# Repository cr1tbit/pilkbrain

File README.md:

# pilkbrain

The schematic is still a bit messy, just for the reference for now.

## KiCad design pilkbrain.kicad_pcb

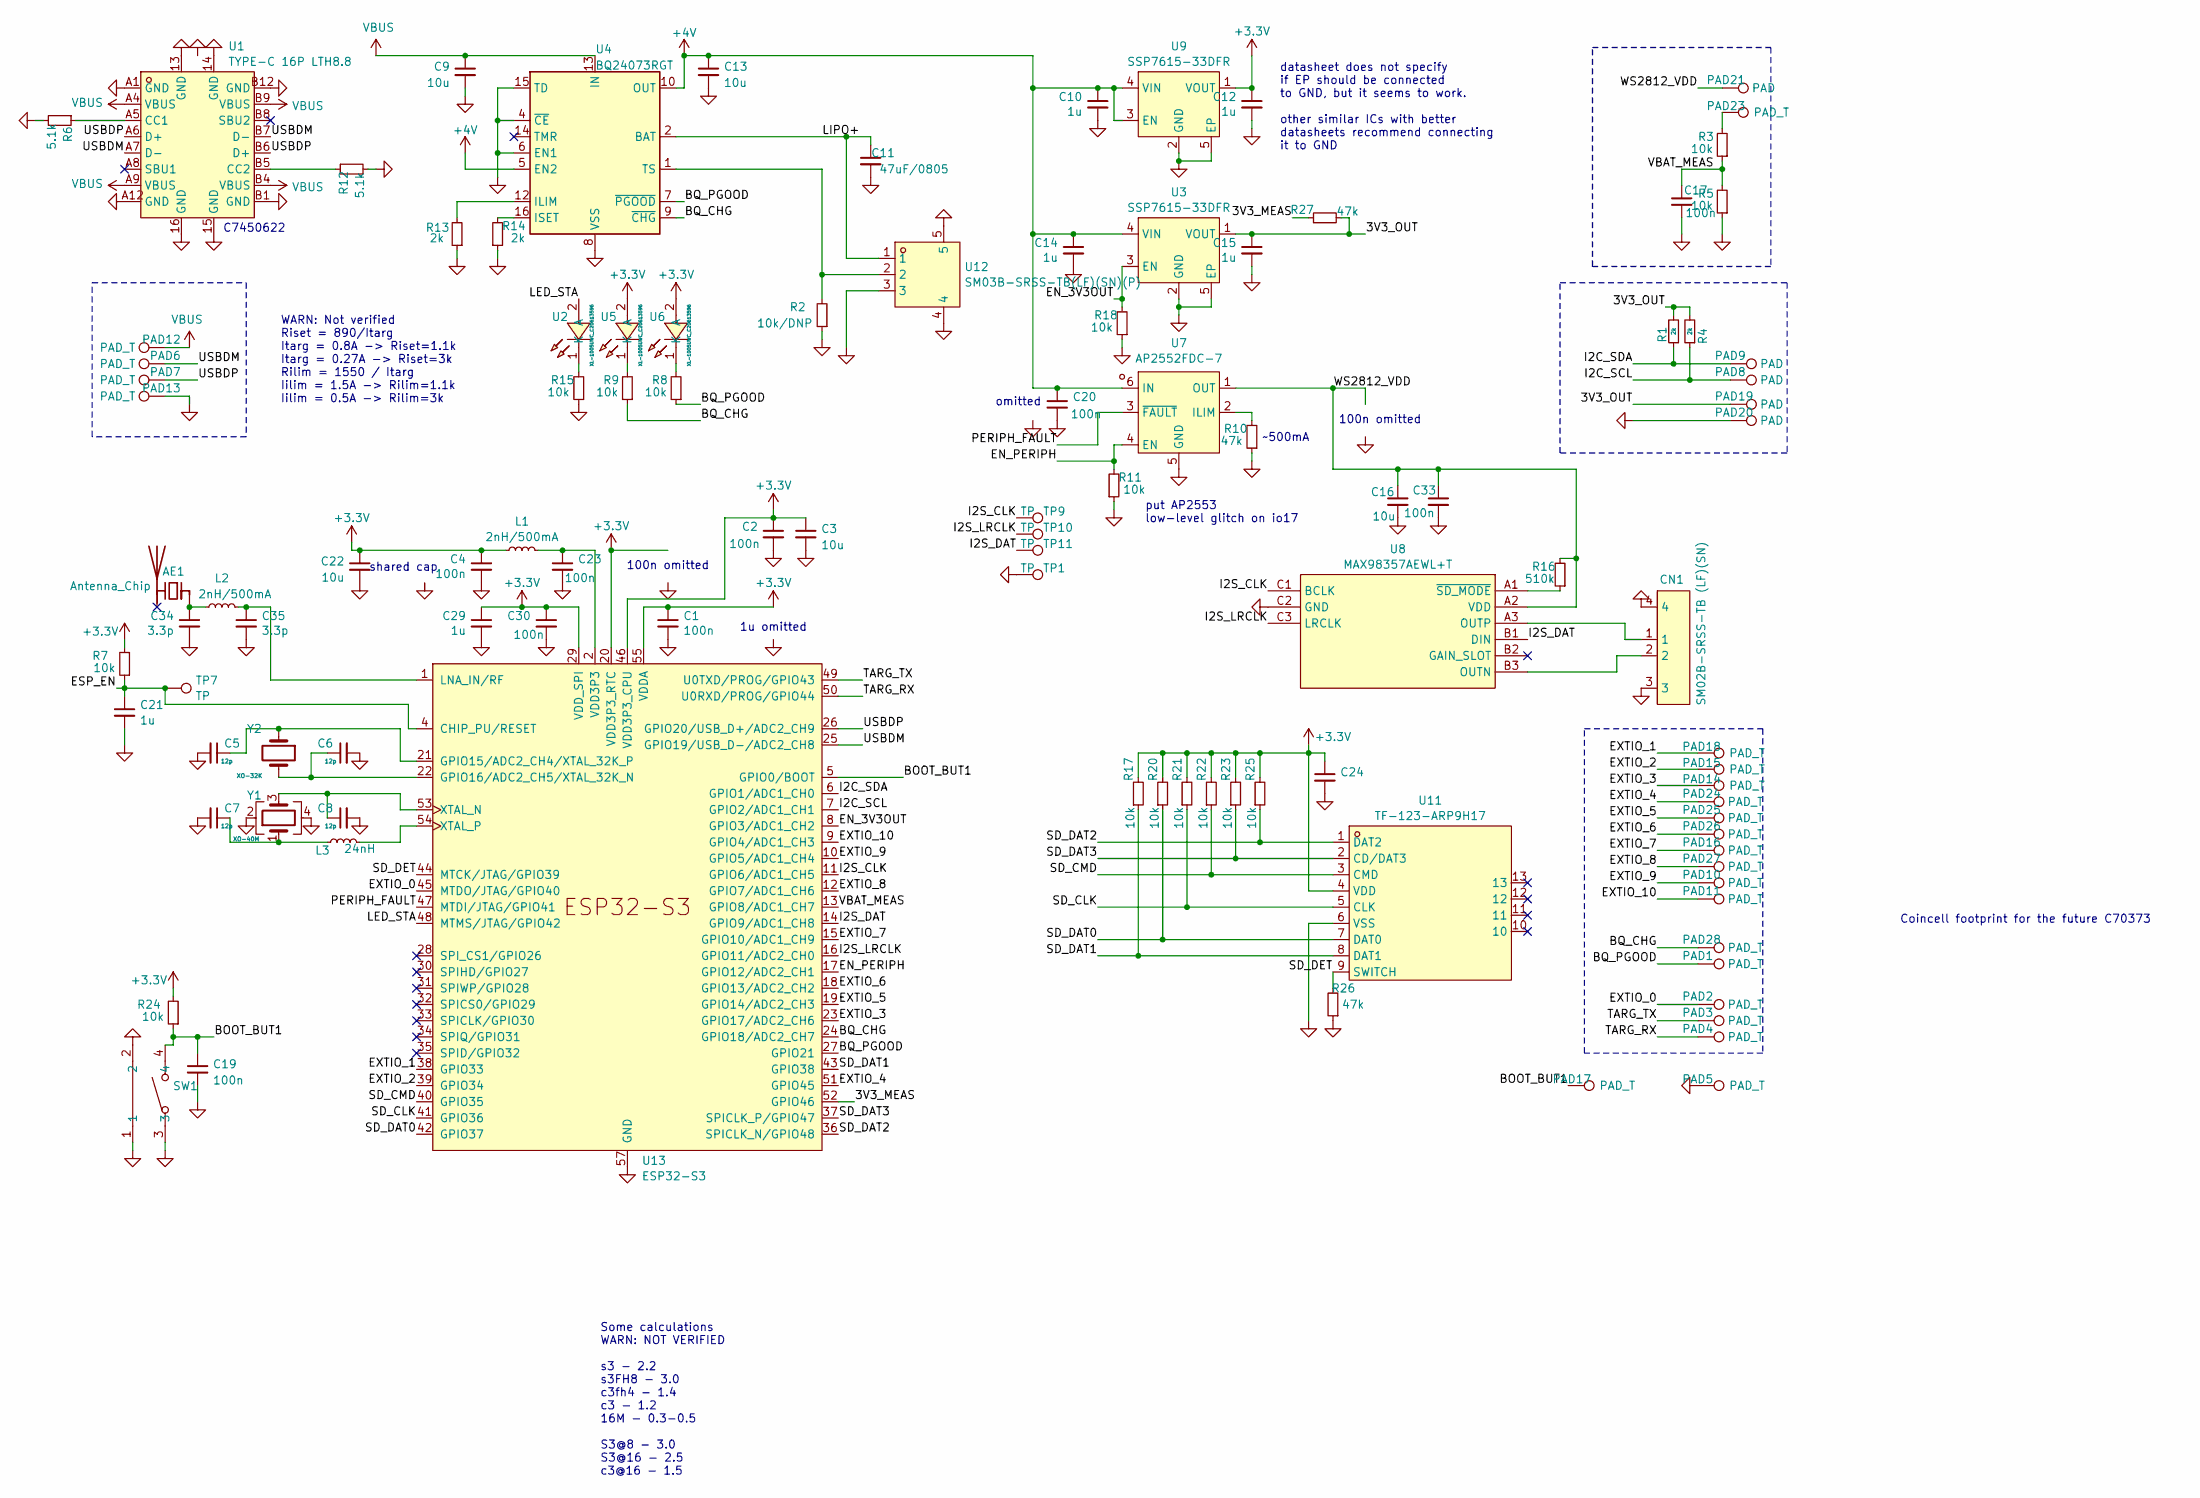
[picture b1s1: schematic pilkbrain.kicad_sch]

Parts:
AE1: Antenna_Chip; Johanson_2450AT18x100; LCSC C127629
C1, C2, C4, C17, C19, C20, C23, C24, C30, C33: 100n; C_0402_1005Metric; LCSC C1525
C3, C9, C13, C16, C22: 10u; C_0402_1005Metric; LCSC C15525
C5, C6, C7, C8: 12p; C_0402_1005Metric; LCSC C1547
C10, C12, C14, C15, C21, C29: 1u; C_0402_1005Metric; LCSC C52923
C11: 47uF/0805; C_0805_2012Metric; LCSC C16780
C34, C35: 3.3p; C_0402_1005Metric; LCSC C1565
CN1: SM02B-SRSS-TB (LF)(SN); CONN-SMD_2P-P1.00_SM02B-SRSS-TB-LF-SN; LCSC C160402
L1, L2: 2nH/500mA; L_0402_1005Metric; LCSC C97984
L3: 24nH; L_0402_1005Metric; LCSC C330863
PAD1, PAD2, PAD3, PAD4, PAD5, PAD6, PAD7, PAD10, PAD11, PAD12, PAD13, PAD14, PAD15, PAD16, PAD17, PAD18, PAD23, PAD24, PAD25, PAD26, PAD27, PAD28: PAD_T; diy_castellate_tight
PAD8, PAD9, PAD19, PAD20, PAD21: PAD; diy_castellate_2.54
R1, R4, R13, R14: 2k; R_0402_1005Metric
R2: 10k/DNP; R_0603_1608Metric
R3, R5, R7, R8, R9, R11, R15, R17, R18, R20, R21, R22, R23, R24, R25: 10k; R_0402_1005Metric
R6, R12: 5.1k; R_0402_1005Metric
R10, R26, R27: 47k; R_0402_1005Metric
R16: 510k; R_0603_1608Metric
SW1: TS24CA; SW-SMD_TS24CA; LCSC C393942
TP1, TP7, TP9, TP10, TP11: TP; TestPoint_Pad_D1.0mm
U1: TYPE-C 16P LTH8.8; USB-C-SMD_TYPE-C-16P-LTH8.8; LCSC C5187469
U2, U5, U6: XL-1005UWC_C20613596; LED0402-RD_YELLOW; LCSC C20613596
U3, U9: SSP7615-33DFR; DFN-4_L1.0-W1.0-P0.65-BL-EP; LCSC C3011523
U4: BQ24073RGT; VQFN-16-1EP_3x3mm_P0.5mm_EP1.6x1.6mm_ThermalVias; LCSC C15220
U7: AP2552FDC-7; WDFN-6_L2.0-W2.0-P0.65-BL-EP-1; LCSC C211419
U8: MAX98357AEWL+T; WLP-9_L1.4-W1.3-P0.40-R3-C3-BR; LCSC C2682619
U11: TF-123-ARP9H17; TF-SMD_TF-123-ARP9H15; LCSC C2982548
U12: SM03B-SRSS-TB(LF)(SN)(P); CONN-SMD_SM03B-SRSS-TB-LF-SN-P; LCSC C160403
U13: ESP32-S3; QFN-56-1EP_7x7mm_P0.4mm_EP5.6x5.6mm; LCSC C3013940
Y1: XO-40M; Crystal_SMD_2520-4Pin_2.5x2.0mm; LCSC C2885592
Y2: XO-32K; Crystal_SMD_2012-2Pin_2.0x1.2mm; LCSC C7500573

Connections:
+3.3V: C1.1, C2.1, C3.1, C4.1, C12.1, C22.1, C24.1, C29.1, C30.1, L1.1, R7.2, R17.2, R20.2, R21.2, R22.2, R23.2, R24.2, R25.2, U5.2 (A), U6.2 (A), U9.1 (VOUT), U11.4 (VDD), U13.20 (VDD3P3_RTC), U13.29 (VDD_SPI), U13.46 (VDD3P3_CPU), U13.55 (VDDA), U13.56 (VDDA)
+4V: C10.1, C13.1, C14.1, C20.1, U3.4 (VIN), U4.5 (EN2), U4.10 (OUT), U4.11 (OUT), U7.6 (IN), U9.3 (EN), U9.4 (VIN)
/3V3_MEAS: R27.1, U13.52 (GPIO46)
/3V3_OUT: C15.1, PAD19.1, R1.2, R4.2, R27.2, U3.1 (VOUT)
/BOOT_BUT1: C19.1, PAD17.1, R24.1, SW1.4, U13.5 (GPIO0/BOOT)
/BQ_CHG: PAD28.1, R9.1, U4.9 (~CHG), U13.24 (GPIO18/ADC2_CH7)
/BQ_PGOOD: PAD1.1, R8.1, U4.7 (~PGOOD), U13.27 (GPIO21)
/EN_3V3OUT: R18.2, U3.3 (EN), U13.8 (GPIO3/ADC1_CH2)
/EN_PERIPH: R11.2, U7.4 (EN), U13.17 (GPIO12/ADC2_CH1)
/ESP_EN: C21.1, R7.1, TP7.1, U13.4 (CHIP_PU/RESET)
/EXTIO_0: PAD2.1, U13.45 (MTDO/JTAG/GPIO40)
/EXTIO_1: PAD18.1, U13.38 (GPIO33)
/EXTIO_2: PAD15.1, U13.39 (GPIO34)
/EXTIO_3: PAD14.1, U13.23 (GPIO17/ADC2_CH6)
/EXTIO_4: PAD24.1, U13.51 (GPIO45)
/EXTIO_5: PAD25.1, U13.19 (GPIO14/ADC2_CH3)
/EXTIO_6: PAD26.1, U13.18 (GPIO13/ADC2_CH2)
/EXTIO_7: PAD16.1, U13.15 (GPIO10/ADC1_CH9)
/EXTIO_8: PAD27.1, U13.12 (GPIO7/ADC1_CH6)
/EXTIO_9: PAD10.1, U13.10 (GPIO5/ADC1_CH4)
/EXTIO_10: PAD11.1, U13.9 (GPIO4/ADC1_CH3)
/I2C_SCL: PAD8.1, R4.1, U13.7 (GPIO2/ADC1_CH1)
/I2C_SDA: PAD9.1, R1.1, U13.6 (GPIO1/ADC1_CH0)
/I2S_CLK: TP9.1, U8.C1 (BCLK), U13.11 (GPIO6/ADC1_CH5)
/I2S_DAT: TP11.1, U8.B1 (DIN), U13.14 (GPIO9/ADC1_CH8)
/I2S_LRCLK: TP10.1, U8.C3 (LRCLK), U13.16 (GPIO11/ADC2_CH0)
/LED_STA: U2.2 (A), U13.48 (MTMS/JTAG/GPIO42)
/LIPO+: C11.1, U4.2 (BAT), U4.3 (BAT), U12.1
/PERIPH_FAULT: U7.3 (~FAULT), U13.47 (MTDI/JTAG/GPIO41)
/SD_CLK: R21.1, U11.5 (CLK), U13.41 (GPIO36)
/SD_CMD: R22.1, U11.3 (CMD), U13.40 (GPIO35)
/SD_DAT0: R20.1, U11.7 (DAT0), U13.42 (GPIO37)
/SD_DAT1: R17.1, U11.8 (DAT1), U13.43 (GPIO38)
/SD_DAT2: R25.1, U11.1 (DAT2), U13.36 (SPICLK_N/GPIO48)
/SD_DAT3: R23.1, U11.2 (CD/DAT3), U13.37 (SPICLK_P/GPIO47)
/SD_DET: R26.2, U11.9 (SWITCH), U13.44 (MTCK/JTAG/GPIO39)
/TARG_RX: PAD4.1, U13.50 (U0RXD/PROG/GPIO44)
/TARG_TX: PAD3.1, U13.49 (U0TXD/PROG/GPIO43)
/USBDM: PAD6.1, U1.A7 (D-), U1.B7 (D-), U13.25 (GPIO19/USB_D-/ADC2_CH8)
/USBDP: PAD7.1, U1.A6 (D+), U1.B6 (D+), U13.26 (GPIO20/USB_D+/ADC2_CH9)
/VBAT_MEAS: C17.1, R3.1, R5.2, U13.13 (GPIO8/ADC1_CH7)
/WS2812_VDD: C16.1, C33.1, PAD21.1, R16.2, U7.1 (OUT), U8.A2 (VDD)
GND: C1.2, C2.2, C3.2, C4.2, C5.2, C6.2, C7.2, C8.2, C9.2, C10.2, C11.2, C12.2, C13.2, C14.2, C15.2, C16.2, C17.2, C19.2, C20.2, C21.2, C22.2, C23.2, C24.2, C29.2, C30.2, C33.2, C34.2, C35.2, CN1.3, CN1.4, PAD5.1, PAD13.1, PAD20.1, R2.1, R5.1, R6.2, R10.1, R11.1, R12.2, R13.1, R14.1, R15.1, R18.1, R26.1, SW1.1, SW1.2, SW1.3, TP1.1, U1.13 (GND), U1.14 (GND), U1.15 (GND), U1.16 (GND), U1.A1 (GND), U1.A12 (GND), U1.B1 (GND), U1.B12 (GND), U3.2 (GND), U3.5 (EP), U4.4 (~CE), U4.6 (EN1), U4.8 (VSS), U4.15 (TD), U4.17 (VSS), U7.5 (GND), U7.7 (EXP), U8.C2 (GND), U9.2 (GND), U9.5 (EP), U11.6 (VSS), U12.3, U12.4, U12.5, U13.57 (GND), Y1.2, Y1.4
unnamed: AE1.1 (FEED), C34.1, L2.1
unnamed: C7.1, L3.1, Y1.1
unnamed: PAD23.1, R3.2
unnamed: R6.1, U1.A5 (CC1)
unnamed: R12.1, U1.B5 (CC2)
unnamed: R15.2, U2.1 (K)
unnamed: R13.2, U4.12 (ILIM)
unnamed: R14.2, U4.16 (ISET)
unnamed: R2.2, U4.1 (TS), U12.2
unnamed: R9.2, U5.1 (K)
unnamed: R8.2, U6.1 (K)
unnamed: R10.2, U7.2 (ILIM)
unnamed: CN1.2, U8.B3 (OUTN)
unnamed: CN1.1, U8.A3 (OUTP)
unnamed: R16.1, U8.A1 (~SD_MODE)
unnamed: C5.1, U13.21 (GPIO15/ADC2_CH4/XTAL_32K_P), Y2.1
unnamed: C6.1, U13.22 (GPIO16/ADC2_CH5/XTAL_32K_N), Y2.2
unnamed: C35.1, L2.2, U13.1 (LNA_IN/RF)
unnamed: C8.1, U13.53 (XTAL_N), Y1.3
unnamed: L3.2, U13.54 (XTAL_P)
VBUS: C9.1, PAD12.1, U1.A4 (VBUS), U1.A9 (VBUS), U1.B4 (VBUS), U1.B9 (VBUS), U4.13 (IN)
VDD3P3: C23.1, L1.2, U13.2 (VDD3P3), U13.3 (VDD3P3)

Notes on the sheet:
put AP2553 low-level glitch on io17
100n omitted
datasheet does not specify if EP should be connected to GND, but it seems to work. other similar ICs with better datasheets recommend connecting it to GND
Some calculations WARN: NOT VERIFIED s3 - 2.2 s3FH8 - 3.0 c3fh4 - 1.4 c3 - 1.2 16M - 0.3-0.5 S3@8 - 3.0 S3@16 - 2.5 c3@16 - 1.5
shared cap
Coincell footprint for the future C70373
WARN: Not verified Riset = 890/Itarg Itarg = 0.8A -> Riset=1.1k Itarg = 0.27A -> Riset=3k Rilim = 1550 / Itarg Iilim = 1.5A -> Rilim=1.1k Iilim = 0.5A -> Rilim=3k
omitted
C7450622
~500mA
1u omitted

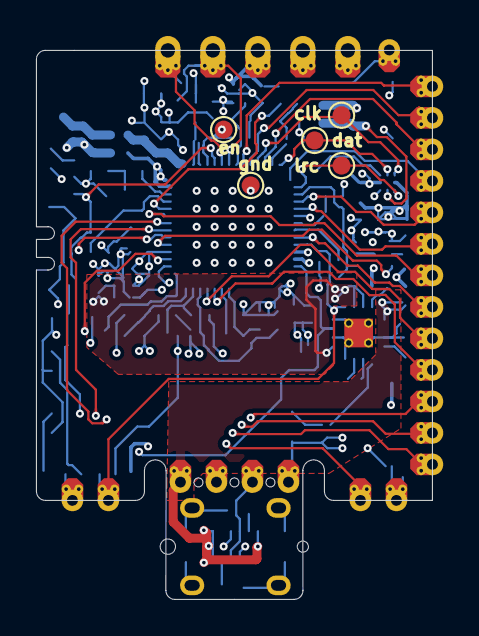
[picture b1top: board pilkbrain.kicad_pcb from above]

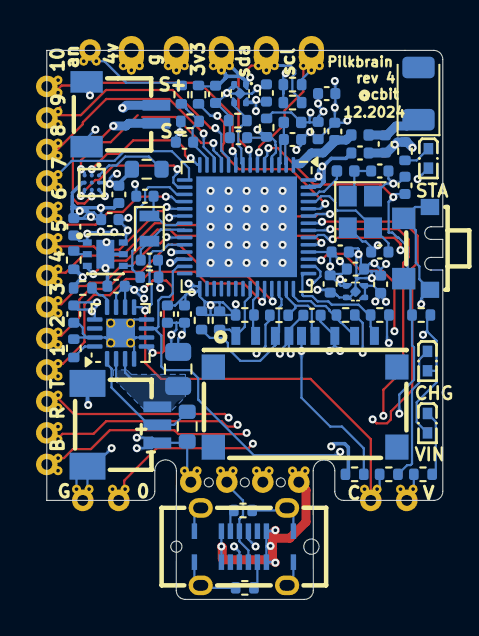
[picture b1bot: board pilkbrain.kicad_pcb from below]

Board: 4 copper layers, 22.0 x 30.5 mm, 106 parts (101 on the bottom side), 65 nets.

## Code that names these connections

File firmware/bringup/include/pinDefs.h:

#pragma once

const int SD_CLK = 33;
const int SD_CMD = 34;
const int SD_D0  = 35;
const int SD_D1  = 36;
const int SD_D2  = 21;
const int SD_D3  = 48;
const int SD_DET  = 3;

// const int I2C_SDA = 41;
// const int I2C_SCL = 40;

const int I2C_SDA = 47;
const int I2C_SCL = 35;


const int BQ_CHG = 39;
const int BQ_PGOOD = 38;

const int WS2812_OUT = 4;
const int EN_PERIPH = 11;
const int VBAT_MEAS = 18;
const int EN_3V3OUT = 7;

const int LED_STAT = 8;
const int BUT2 = 42;
const int BOOT_BUT1 = 0;

const int EXTIO_1 = 6;
const int EXTIO_2 = 5;
const int EXTIO_3 = 14;
const int EXTIO_4 = 13;
const int EXTIO_5 = 12;
const int EXTIO_6 = 2;
const int EXTIO_7 = 10;
const int EXTIO_8 = 9;

// const int I2S_DAT = 17;
// const int I2S_LRCLK = 45;
// const int I2S_CLK = 47;

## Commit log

2024-10-03 add files, save before move to s3
2024-10-05 before route
2024-10-06 before move 4L
2024-10-12 before fab out
2024-10-15 order(?)
2024-10-21 new formfactor placement etc
2024-10-27 rev2 prod?
2024-11-25 3rd redo but good this time
2024-11-27 before order
2024-11-28 wrong holes
2024-12-07 another element swappage
2024-12-08 finish route?
2024-12-31 little schematic cleanup, add PDF and render image
2025-05-08 PoC OLED + audio
